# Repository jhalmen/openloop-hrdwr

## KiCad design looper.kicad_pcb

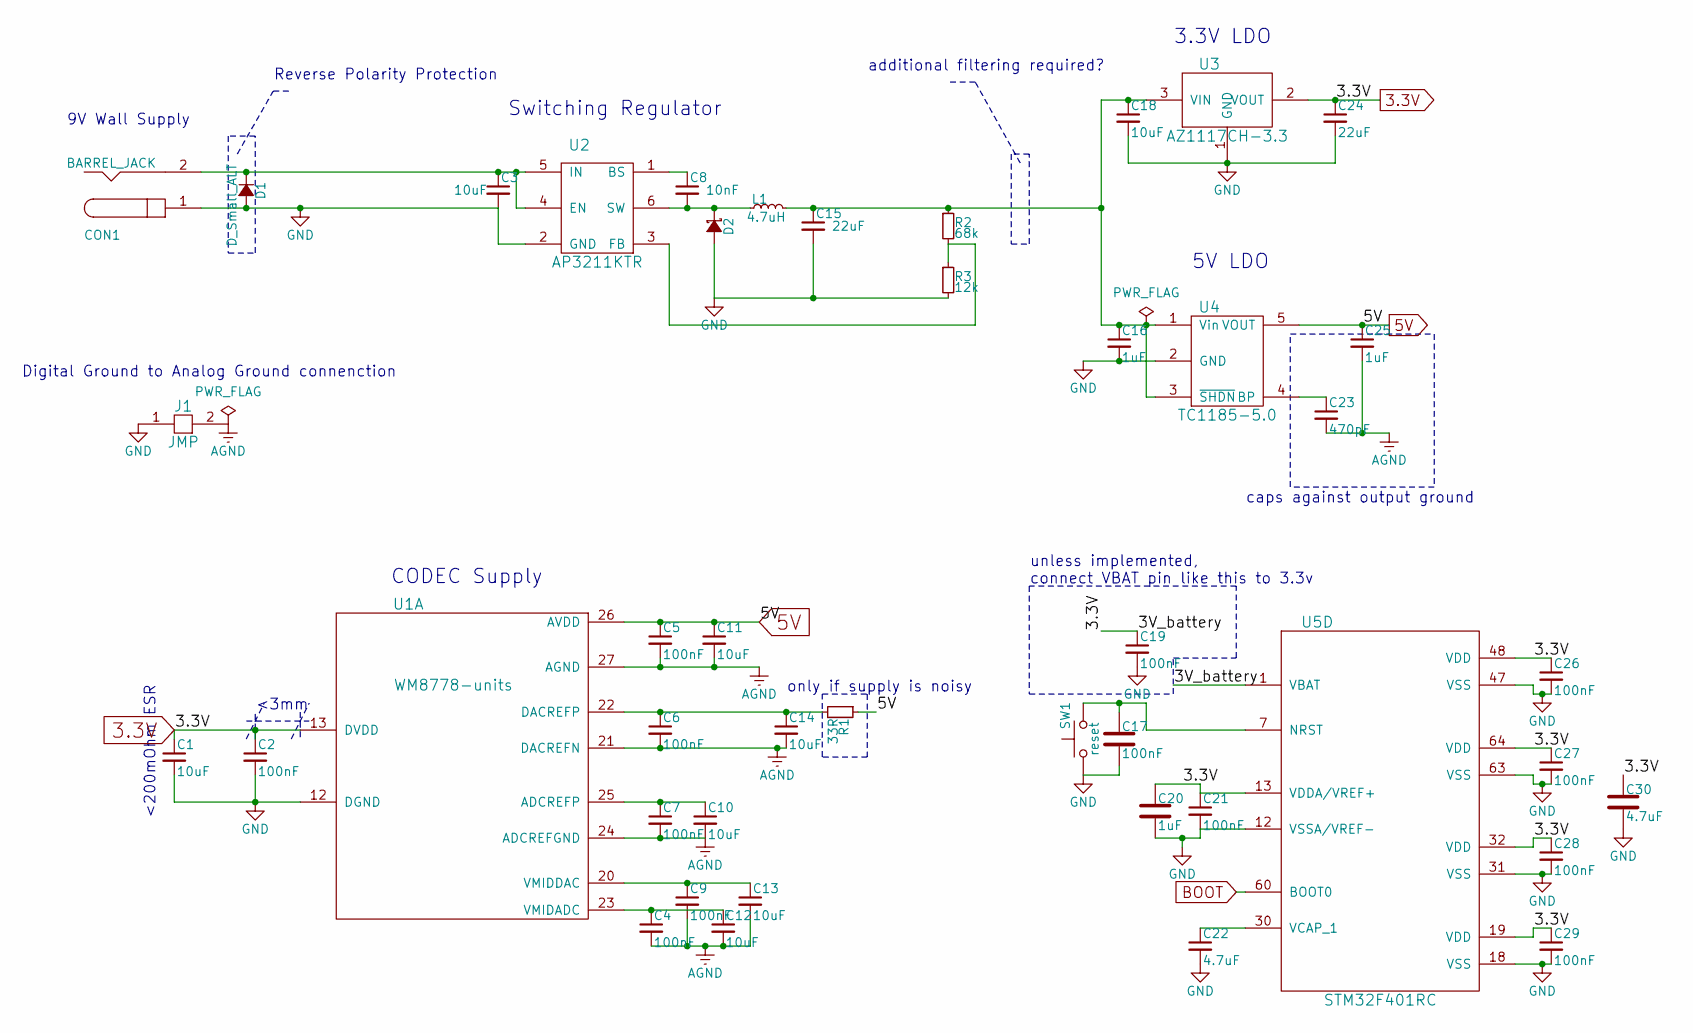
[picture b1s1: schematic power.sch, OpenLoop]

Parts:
C1, C3, C10, C11, C12, C13, C14, C18: 10uF; C_0805_HandSoldering
C2, C4, C5, C6, C7, C9, C17, C19, C21, C26, C27, C28, C29: 100nF; C_0805_HandSoldering
C8: 10nF; C_0805_HandSoldering
C15, C24: 22uF; C_0805_HandSoldering
C16, C20, C25: 1uF; C_0805_HandSoldering
C22, C30: 4.7uF; C_0805_HandSoldering
C23: 470pF; C_0805_HandSoldering
CON1: BARREL_JACK; PJ-037A
D1: D_Small_ALT; D_DO-35_SOD27_P7.62mm_Horizontal
D2: D_Schottky_Small_ALT; D_DO-35_SOD27_P7.62mm_Horizontal
J1: JMP; netconnector
L1: 4.7uH; Resistor_SMDuniversal_0805to1206_HandSoldering
R1: 33R; R_Axial_DIN0207_L6.3mm_D2.5mm_P7.62mm_Horizontal
R2: 68k; R_Axial_DIN0207_L6.3mm_D2.5mm_P7.62mm_Horizontal
R3: 12k; R_Axial_DIN0207_L6.3mm_D2.5mm_P7.62mm_Horizontal
SW1: reset; SW_PUSH_6mm
U1: WM8778-units; SSOP-28_5.3x10.2mm_Pitch0.65mm_HandSolder
U2: AP3211KTR; SOT-23-6_Handsoldering
U3: AZ1117CH-3.3; SOT-223-3Lead_TabPin2_HandSoldering
U4: TC1185-5.0; SOT-23-5_HandSoldering
U5: STM32F401RC; LQFP-64_10x10mm_Pitch0.5mm_HandSolder

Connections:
3.3V: C1.1, C2.1, C19.1, C20.1, C21.1, C24.1, C26.1, C27.1, C28.1, C29.1, C30.1, U1.13 (DVDD), U3.2 (VOUT), U5.1 (VBAT), U5.13 (VDDA/VREF+), U5.19 (VDD), U5.32 (VDD), U5.48 (VDD), U5.64 (VDD); also elsewhere on the board
5V: C5.1, C11.1, C25.1, R1.1, U1.26 (AVDD), U4.5 (VOUT); also elsewhere on the board
BOOT: U5.60 (BOOT0); also elsewhere on the board
GND: C1.2, C2.2, C3.2, C15.2, C16.2, C17.2, C18.2, C19.2, C20.2, C21.2, C22.2, C24.2, C26.2, C27.2, C28.2, C29.2, C30.2, CON1.1, D1.2 (A), D2.2 (A), J1.1, R3.2, SW1.1, U1.12 (DGND), U2.2 (GND), U3.1 (GND), U4.2 (GND), U5.12 (VSSA/VREF-), U5.18 (VSS), U5.31 (VSS), U5.47 (VSS), U5.63 (VSS); also elsewhere on the board
unnamed: C3.1, CON1.2, D1.1 (K), U2.4 (EN), U2.5 (IN)
unnamed: C8.1, U2.1 (BS)
unnamed: C8.2, D2.1 (K), L1.1, U2.6 (SW)
unnamed: C7.1, C10.1, U1.25 (ADCREFP)
unnamed: C4.1, C12.1, U1.23 (VMIDADC)
unnamed: C9.1, C13.1, U1.20 (VMIDDAC)
unnamed: C6.1, C14.1, R1.2, U1.22 (DACREFP)
unnamed: C15.1, C16.1, C18.1, L1.2, R2.1, U3.3 (VIN), U4.1 (Vin), U4.3 (~SHDN)
unnamed: C17.1, SW1.2, U5.7 (NRST)
unnamed: C22.1, U5.30 (VCAP_1)
unnamed: C23.1, U4.4 (BP)
unnamed: R2.2, R3.1, U2.3 (FB)

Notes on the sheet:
Digital Ground to Analog Ground connenction
9V Wall Supply
Reverse Polarity Protection
additional filtering required?
<3mm
<200mOhm ESR
only if supply is noisy
CODEC Supply
Switching Regulator
3.3V LDO
5V LDO
caps against output ground
unless implemented, connect VBAT pin like this to 3.3v

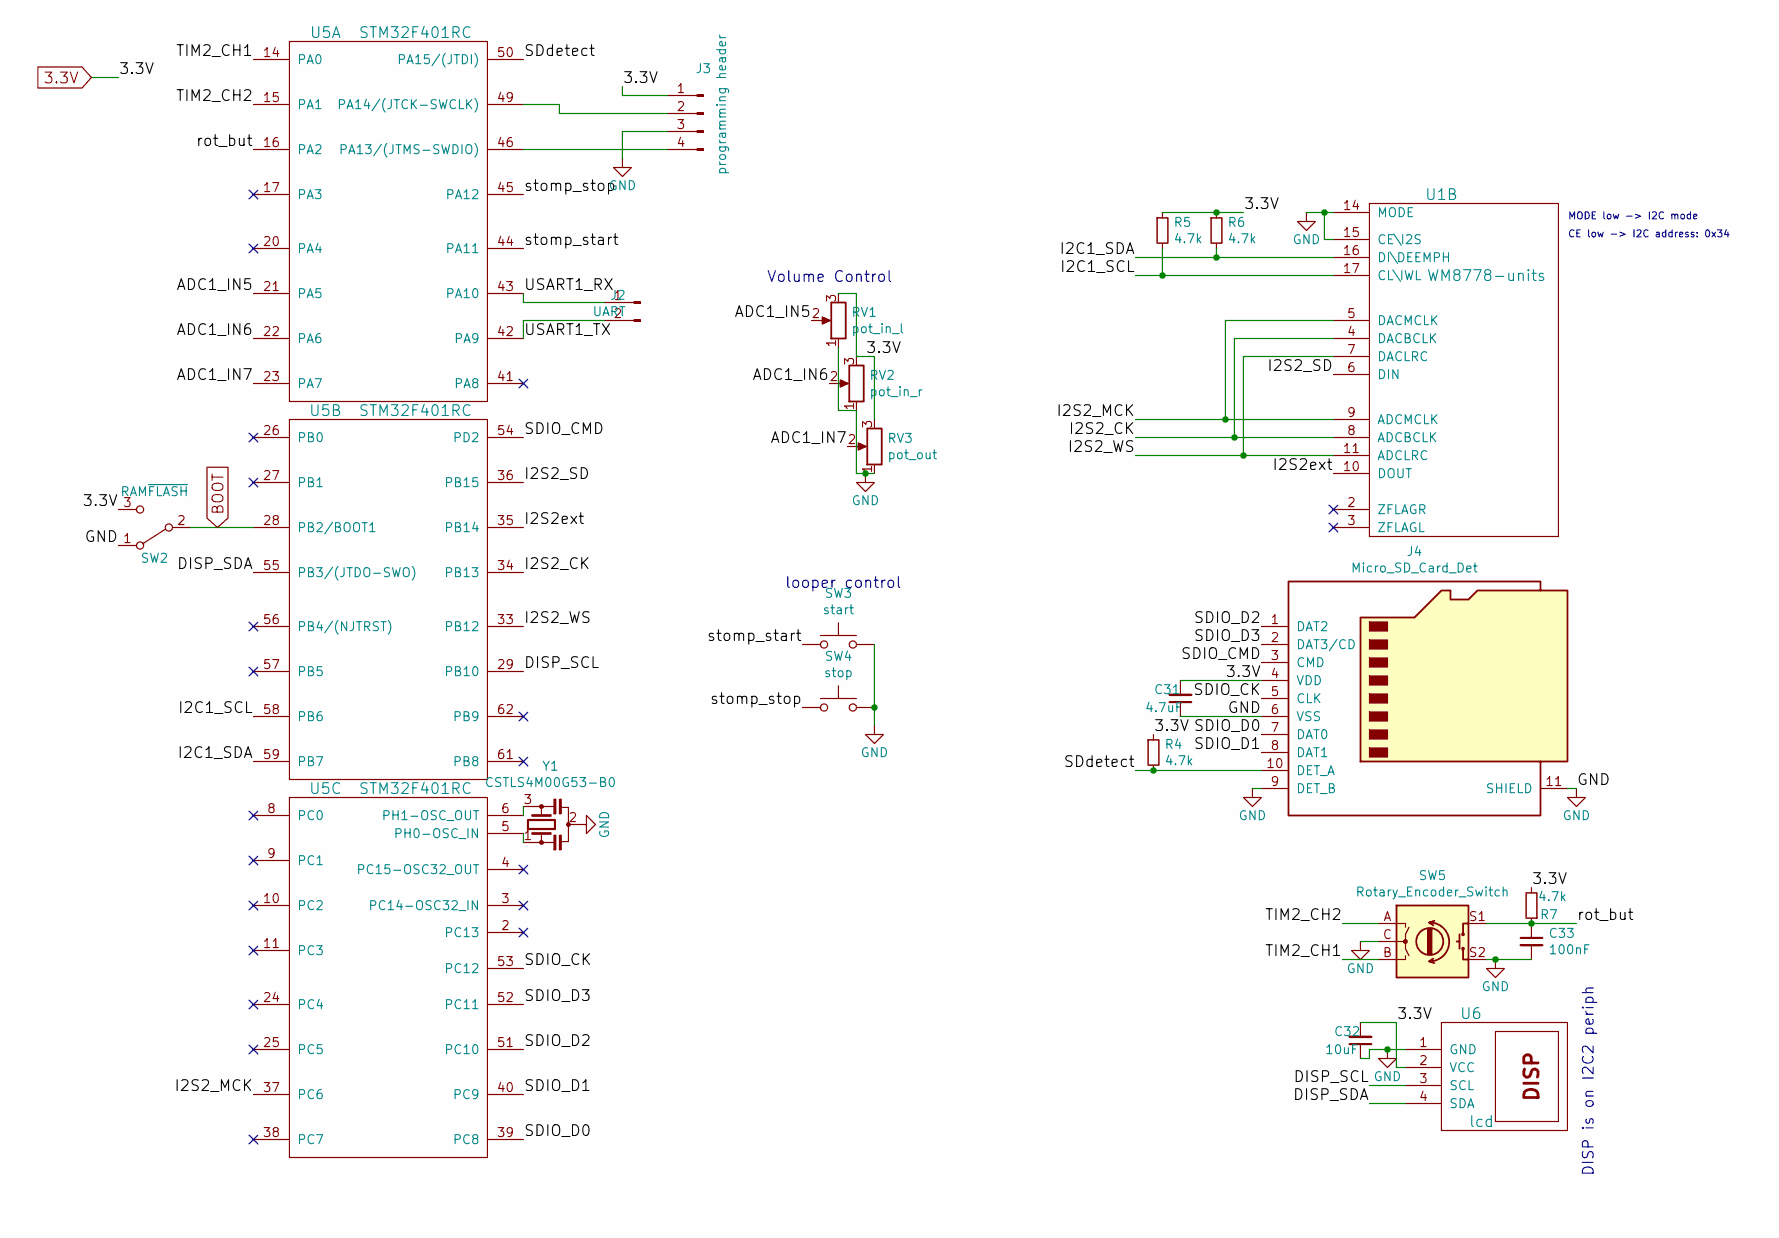
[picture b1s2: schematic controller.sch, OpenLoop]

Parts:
C31: 4.7uF; C_0805_HandSoldering
C32: 10uF; C_0805_HandSoldering
C33: 100nF; C_0805_HandSoldering
J2: UART; Pin_Header_Straight_1x02_Pitch2.54mm
J3: programming header; Pin_Header_Straight_1x04_Pitch2.54mm
J4: Micro_SD_Card_Det; SD-503182_Molex_micro_SD_HandSolder
R4, R5, R6, R7: 4.7k; R_Axial_DIN0207_L6.3mm_D2.5mm_P7.62mm_Horizontal
RV1: pot_in_l; Potentiometer_WirePads_Small
RV2: pot_in_r; Potentiometer_WirePads_Small
RV3: pot_out; Potentiometer_WirePads_Small
SW2: RAM~FLASH; SW_Micro_SPST
SW3: start; SW_PUSH_6mm
SW4: stop; SW_PUSH_6mm
SW5: Rotary_Encoder_Switch; EN11-HSM
U1: WM8778-units; SSOP-28_5.3x10.2mm_Pitch0.65mm_HandSolder
U5: STM32F401RC; LQFP-64_10x10mm_Pitch0.5mm_HandSolder
U6: lcd; Socket_Strip_Straight_1x04_Pitch2.54mm
Y1: CSTLS4M00G53-B0; Resonator_muRata_CSTLSxxxG-3pin_w8.0mm_h3.0mm

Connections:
3.3V: C31.2, C32.2, J3.1, J4.4 (VDD), R4.1, R5.1, R6.1, R7.2, RV1.3, RV2.3, RV3.3, SW2.3 (C), U6.2 (VCC); also elsewhere on the board
/controller/ADC1_IN5: RV1.2, U5.21 (PA5)
/controller/ADC1_IN6: RV2.2, U5.22 (PA6)
/controller/ADC1_IN7: RV3.2, U5.23 (PA7)
/controller/DISP_SCL: U5.29 (PB10), U6.3 (SCL)
/controller/DISP_SDA: U5.55 (PB3/(JTDO-SWO)), U6.4 (SDA)
/controller/I2C1_SCL: R5.2, U1.17 (CL\IWL), U5.58 (PB6)
/controller/I2C1_SDA: R6.2, U1.16 (DI\DEEMPH), U5.59 (PB7)
/controller/I2S2_CK: U1.4 (DACBCLK), U1.8 (ADCBCLK), U5.34 (PB13)
/controller/I2S2_MCK: U1.5 (DACMCLK), U1.9 (ADCMCLK), U5.37 (PC6)
/controller/I2S2_SD: U1.6 (DIN), U5.36 (PB15)
/controller/I2S2_WS: U1.7 (DACLRC), U1.11 (ADCLRC), U5.33 (PB12)
/controller/I2S2ext: U1.10 (DOUT), U5.35 (PB14)
/controller/SDIO_CK: J4.5 (CLK), U5.53 (PC12)
/controller/SDIO_CMD: J4.3 (CMD), U5.54 (PD2)
/controller/SDIO_D0: J4.7 (DAT0), U5.39 (PC8)
/controller/SDIO_D1: J4.8 (DAT1), U5.40 (PC9)
/controller/SDIO_D2: J4.1 (DAT2), U5.51 (PC10)
/controller/SDIO_D3: J4.2 (DAT3/CD), U5.52 (PC11)
/controller/SDdetect: J4.10 (DET_A), R4.2, U5.50 (PA15/(JTDI))
/controller/TIM2_CH1: SW5.B, U5.14 (PA0)
/controller/TIM2_CH2: SW5.A, U5.15 (PA1)
/controller/USART1_RX: J2.1, U5.43 (PA10)
/controller/USART1_TX: J2.2, U5.42 (PA9)
/controller/rot_but: C33.1, R7.1, SW5.S1, U5.16 (PA2)
/controller/stomp_start: SW3.1, U5.44 (PA11)
/controller/stomp_stop: SW4.1, U5.45 (PA12)
BOOT: SW2.2 (B), U5.28 (PB2/BOOT1); also elsewhere on the board
GND: C31.1, C32.1, C33.2, J3.3, J4.6 (VSS), J4.9 (DET_B), J4.11 (SHIELD), RV1.1, RV2.1, RV3.1, SW2.1 (A), SW3.2, SW4.2, SW5.C, SW5.S2, U1.14 (MODE), U1.15 (CE\I2S), U6.1 (GND), Y1.2; also elsewhere on the board
unnamed: J3.2, U5.49 (PA14/(JTCK-SWCLK))
unnamed: J3.4, U5.46 (PA13/(JTMS-SWDIO))
unnamed: U5.5 (PH0-OSC_IN), Y1.1
unnamed: U5.6 (PH1-OSC_OUT), Y1.3

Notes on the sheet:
MODE low -> I2C mode
CE low -> I2C address: 0x34
DISP is on I2C2 periph
Volume Control
looper control

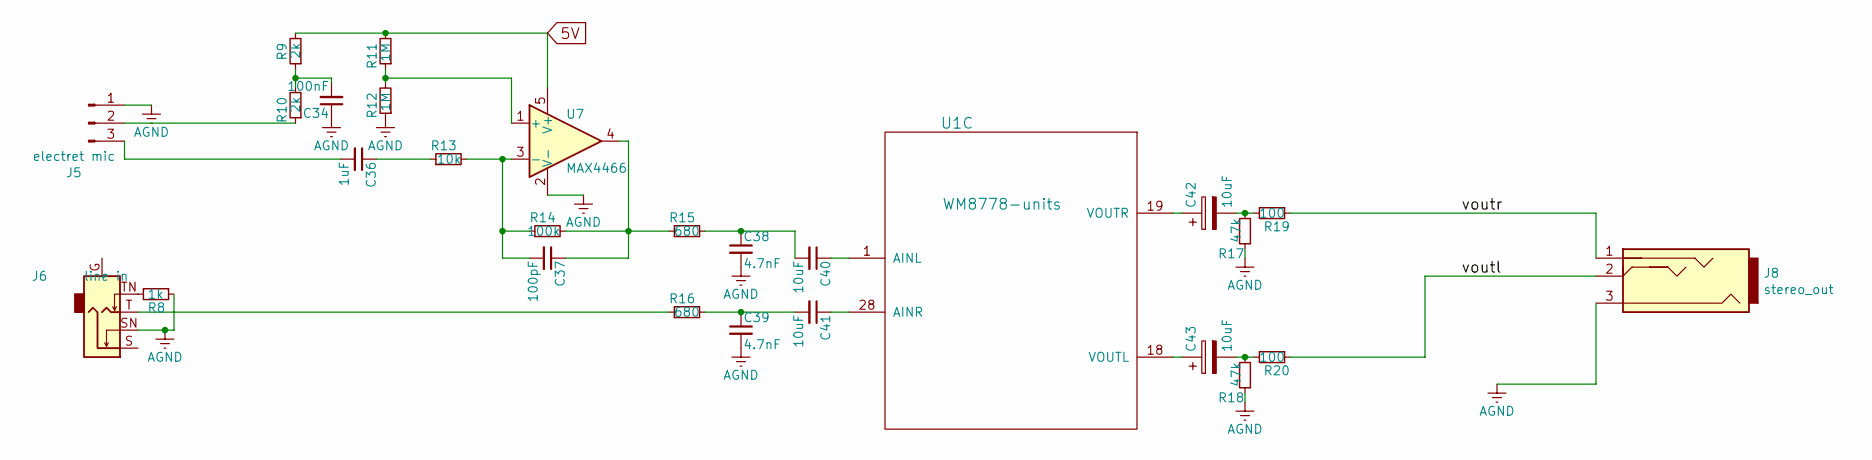
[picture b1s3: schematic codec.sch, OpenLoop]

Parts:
C34: 100nF; C_0805_HandSoldering
C36: 1uF; C_0805_HandSoldering
C37: 100pF; C_0805_HandSoldering
C38, C39: 4.7nF; C_0805_HandSoldering
C40, C41: 10uF; C_0805_HandSoldering
C42, C43: 10uF; CP_Radial_D5.0mm_P2.00mm
J5: electret mic; Socket_Strip_Straight_1x02_Pitch2.54mm
J6: line in; Socket_Strip_Straight_1x03_Pitch2.54mm
J8: stereo_out; Socket_Strip_Straight_1x03_Pitch2.54mm
R8: 1k; R_Axial_DIN0207_L6.3mm_D2.5mm_P7.62mm_Horizontal
R9, R10: 2k; R_Axial_DIN0207_L6.3mm_D2.5mm_P7.62mm_Horizontal
R11, R12: 1M; R_Axial_DIN0207_L6.3mm_D2.5mm_P7.62mm_Horizontal
R13: 10k; R_Axial_DIN0207_L6.3mm_D2.5mm_P7.62mm_Horizontal
R14: 100k; R_Axial_DIN0207_L6.3mm_D2.5mm_P7.62mm_Horizontal
R15, R16: 680; R_Axial_DIN0207_L6.3mm_D2.5mm_P7.62mm_Horizontal
R17, R18: 47k; R_Axial_DIN0207_L6.3mm_D2.5mm_P7.62mm_Horizontal
R19, R20: 100; R_Axial_DIN0207_L6.3mm_D2.5mm_P7.62mm_Horizontal
U1: WM8778-units; SSOP-28_5.3x10.2mm_Pitch0.65mm_HandSolder
U7: MAX4466; SOT-353_SC-70-5_Handsoldering

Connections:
5V: R9.2, R11.2, U7.5 (V+); also elsewhere on the board
/Codec/voutl: J8.2, R20.1; also elsewhere on the board
/Codec/voutr: J8.1, R19.1; also elsewhere on the board
unnamed: C34.2, R9.1, R10.2
unnamed 44: R11.1, R12.2, U7.1 (+); also elsewhere on the board
unnamed 45: J5.2, R10.1; also elsewhere on the board
unnamed: C36.1, R13.1
unnamed 47: C37.1, R14.2, R15.1, U7.4; also elsewhere on the board
unnamed: C37.2, R13.2, R14.1, U7.3 (-)
unnamed: C38.1, C40.2, R15.2
unnamed: C39.1, C41.2, R16.2
unnamed: C40.1, U1.1 (AINL)
unnamed: C41.1, U1.28 (AINR)
unnamed: C42.1, U1.19 (VOUTR)
unnamed: C42.2, R17.2, R19.2
unnamed: C43.1, U1.18 (VOUTL)
unnamed: C43.2, R18.2, R20.2
unnamed: J6.T, R16.1
unnamed: J6.TN, R8.2

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
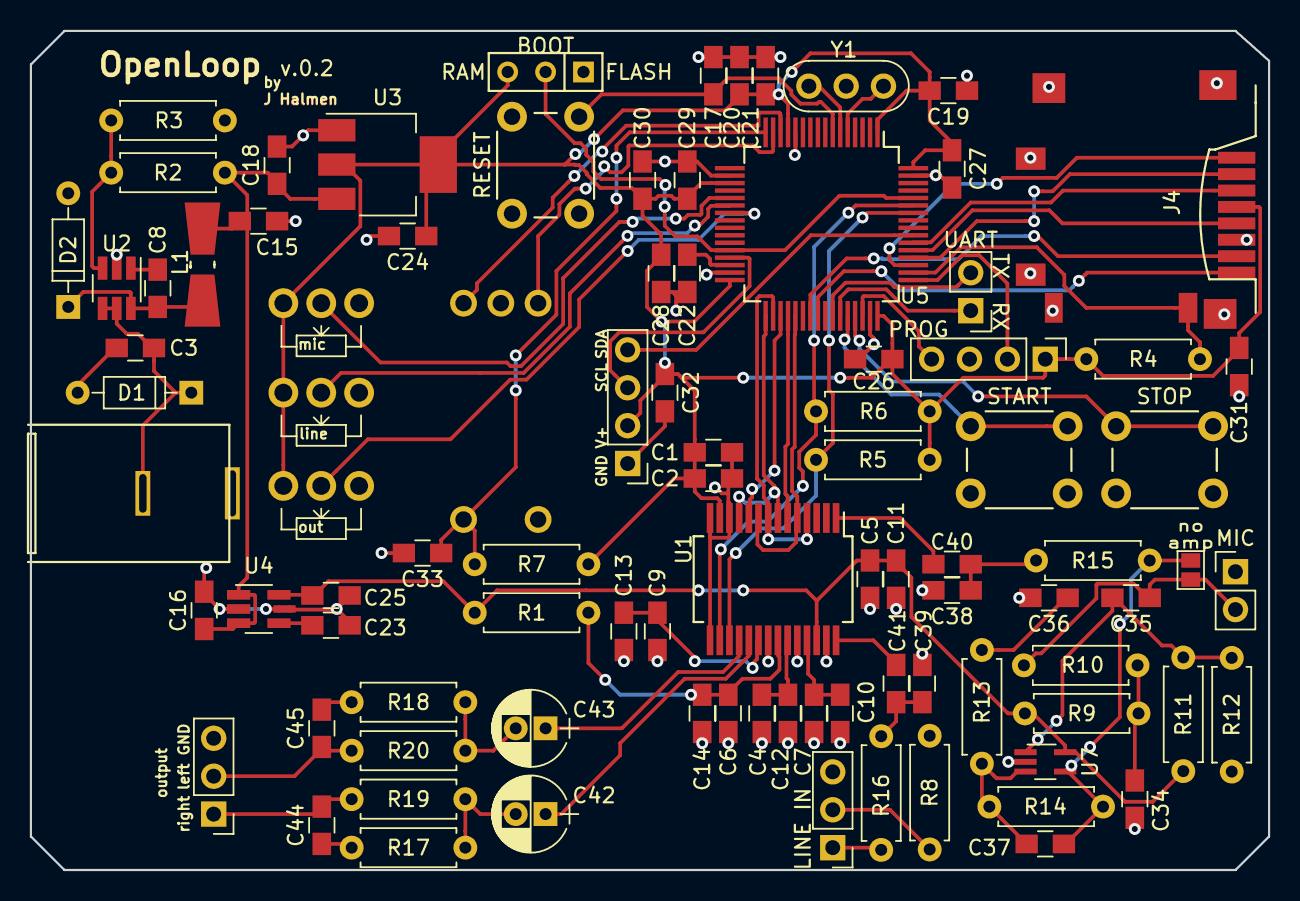
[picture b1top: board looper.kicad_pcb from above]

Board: 2 copper layers, 83.0 x 56.2 mm, 93 parts (0 on the bottom side), 65 nets.

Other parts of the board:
C35: 10nF C0G/NP0; C_0805_HandSoldering
C44, C45: 4.7nF C0G/NP0; C_0805_HandSoldering
J7: line/~mic; GS2

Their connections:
/Codec/voutl: C45.1; also elsewhere on the board
/Codec/voutr: C44.1; also elsewhere on the board
unnamed 44: C35.1; also elsewhere on the board
unnamed 45: C35.2, J7.2; also elsewhere on the board
unnamed 47: J7.1; also elsewhere on the board

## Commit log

2017-05-02 ksch: add buck converter to lib
    add datasheet links for both codec and buck
2017-05-02 ksch: begin drawing schematics
2017-05-02 ksch: use schottky diode for switching regulator
2017-05-02 ksch: add LDOs to lib
2017-05-02 ksch: fix error in codec supply
2017-05-02 ksch: add stm32f401rc to lib
2017-05-02 ksch: add uC power and programming pins
2017-05-02 ksch: add I2S interface connections
2017-06-07 ksch: use i2s2 and i2s3 for codec
2017-06-07 ksch: change to use i2s2 bidirectional, free i2s3
2017-06-07 ksch: add boot0 pin to switch
2017-06-07 ksch: add filter to both analog out channels
2017-06-07 ksch: add codec control interface as i2c1
2017-06-07 ksch: use own page layout
2017-06-07 ksch: remove cached library
2017-09-24 kpcb: start adding footprints
    SSOP28 -- codec
    LQFP64 -- uC
    SD_molex -- uSDcard
2017-09-25 kpcb: add more footprints
2017-09-27 ksch: add stuff that isn't on soldered prototype yet
    this hopefully completes the rev. A schematics
2017-09-27 ksch: reannotate schematics to have a single style of part-naming
2017-09-29 ksch: change power connector to DC5525
2017-09-29 ksch: fix footprintproblem, change some labels
2017-09-29 ksch: change I2S2ext from PC2 to PB14 to make routing easier
2017-09-29 ksch: switch encoder connections to make routing easier
2017-10-01 ksch: move SDdetect pin to PA15 to make routing easier
2017-10-01 ksch: move stomp buttons to make routing easier
2017-10-01 ksch: rotate resistor to make routing easier
2017-10-02 kpcb: fix netconnector footprint
2017-10-02 kpcb: add first pcb design
2017-10-02 k: fix pcb
    power connector trouble
    wrong footprint for caps
2017-10-09 ksch: change component values to include the unit except for resistors add more info to some devices
2018-09-06 fix mirrored sdcard footprints
2018-09-06 pcb: use fixed sd footprints, reroute
2018-09-08 migrate to kicad v5
2019-02-02 ready for print
2019-02-02 update codec schematic: mic power
2020-03-23 add gitignore, schematic lib cache
